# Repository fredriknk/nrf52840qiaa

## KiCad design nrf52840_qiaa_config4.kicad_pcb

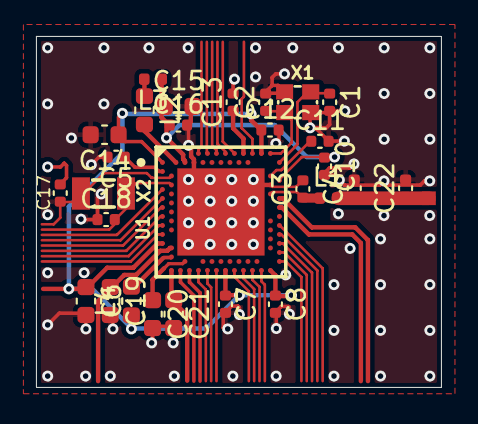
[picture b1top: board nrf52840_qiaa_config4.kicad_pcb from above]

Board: 4 copper layers, 22.5 x 19.5 mm, 28 parts (0 on the bottom side), 12 nets.

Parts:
C1, C2, C17, C18: 12pF; C_0402_1005Metric
C3: 0.8pF; C_0402_1005Metric
C4: 0.5pF; C_0402_1005Metric
C5, C7, C8, C12: 100nF; C_0402_1005Metric
C6, C19, C20, C21: 4.7µF; C_0603_1608Metric
C10, C13, C22: N.C.; C_0402_1005Metric
C11: 100pF; C_0402_1005Metric
C14, C15: 1.0µF; C_0603_1608Metric
C16: 47nF; C_0402_1005Metric
L1: 4.7nH; L_0402_1005Metric
L2, L4: 10µH; L_0603_1608Metric
L3: 15nH; L_0402_1005Metric
U1: nRF52840-QIAA; _Applications_test_rsk_lib_RSK-ONLY_PcbLib_AQFN50P700X700X8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
X1: 32MHz; BT-XTAL_2016
X2: 32.768kHz; _Repositories_Applications_test_rsk_lib_RSK-ONLY_PcbLib_pcb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

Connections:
DEC4_6: C10.1, C15.1, C16.1, L3.1, U1.B5, U1.E24
GND: C1.2, C2.2, C3.2, C4.2, C5.2, C6.2, C7.2, C8.2, C10.2, C11.2, C12.2, C13.2, C14.2, C15.2, C16.2, C17.1, C18.1, C19.2, C20.2, C21.2, C22.2, U1.74, U1.B7, U1.F23
unnamed: L2.1, L3.2
NetC3_2: C3.1, L1.1, U1.H23
P0.00/XL1: U1.D2, X2.1
P0.01/XL2: U1.F2, X2.2
RF: C4.1, C22.1, L1.2
VBUS: C21.1, U1.AD2
VDD_HV: C19.1, U1.Y2
VDD_nRF: C6.1, C7.1, C8.1, C12.1, C14.1, L4.1, U1.A22, U1.AD14, U1.AD23, U1.B1, U1.W1
XC1: C1.1, U1.B24, X1.1 (inp)
XC2: C2.1, U1.A23, X1.3 (out)
